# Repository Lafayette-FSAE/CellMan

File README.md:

# CellMan v2.2
A Cell Management Board for the Lafayette FSAE Accumulator Management System.

The purpose of CellMan is twofold. First, it is responsible for making and reporting
key measurements of the Cell it is mounted to. The most important of these are Voltage 
and Temperature, which are used by PacMan to determine if a fault condition has occured, and can also be used to help estimate State of Charge.
In addition, CellMan is capable of measuring the voltage of its Cell's negative terminal relative to the segment, used for determining its position, 
and some properties of its balancing circuit.

Each CellMan has also been equipped with an experimental Balancing Circuit, which can be used to allow active balancing of Cells within the same segment.
This is done through an isolated flyback converter, which pulls current from the cell it sits on, steps it up to the full segment voltage through an isolated
transformer, and outputs it back to the segment. A CellMan is capable of measuring the current being drawn from the cell by the flyback converter and the
voltage on its output side, and can report these back to PacMan along with the measurements mentioned above.

## Interface

Each CellMan is an I2C slave device, and can be controlled by a master, usually PacMan. All data reported to PacMan is sent over this interface, as well as commands
that control the high level behavior of CellMan.

While CellMan on different segments are electrically isolated from eachother, they occupy the same I2C bus, through 2 isolators on the PacMan board, and so their
addresses cannot conflict

### Reading Data

When data is requested from CellMan, it will report it over the bus, one byte at a time,  and always in the same order. An arbitrary number of bytes can be requested.

Most data is stored as 16 bit integers, and so is sent in 2 byte pairs, with the Least Significant Byte first, and the Most Significant Byte second.

Bytes are sent in the following order:

|Byte|0               |1               |2               |3              |4              |5            |6            |
|----|----------------|----------------|----------------|---------------|---------------|-------------|-------------|
|Data|Firmware Version|Cell Voltage LSB|Cell Voltage MSB|Temperature LSB|Temperature MSB|Position LSB |Position MSB |
|Unit|NA              |mV              |mV              |1/10 ºC        |1/10 ºC        |Raw ADC Value|Raw ADC Value|

Additional data can be added to the end of this as needed.

### Sending Commands

PacMan is controlled by writing data to one or more 16 bit registers. Each write command should be 3 bytes long, a 1 byte address, followed by 2 bytes of data.

Register addresses are organized as follows:

#### Calibration Parameters

While this feature is not currently supported, CellMan will eventually allow configuration of its many calibration functions for maximum accuracy.
Addresses from 0x01 to 0x0F have been reserved for this purpose.

|Address|Description      |
|-------|-----------------|
|0x01   |Temp Slope       |
|0x02   |Temp Offset      |
|0x03   |Balance Current Slope|
|0x04   |Balance Voltage Slope|

#### Balance Circuit

Addresses from 0x11 to 0x1F are reserved for registers which control the behavior of the Balance Circuit.
Currently, the circuit can be enabled or disabled, and the duty cycle and frequency of its control signal
can be changed.
0x14 is reserved for a Target Voltage parameter in order to allow support for a closed loop control scheme
to be used in the future. 

|Address|Description      |
|-------|-----------------|
|0x11   |Balance Enabled  |
|0x12   |Balance Duty Cycle|
|0x13   |Balance Frequency|
|0x14   |Target Voltage   |

#### Debug

0x23 controls the board's green LED, used for Debugging and feedback.

|Address|Description      |
|-------|-----------------|
|0x23   |Debug LED        |

## Schematic
[Link to PDF](https://sites.lafayette.edu/motorsports/files/2019/11/CellMan.pdf)

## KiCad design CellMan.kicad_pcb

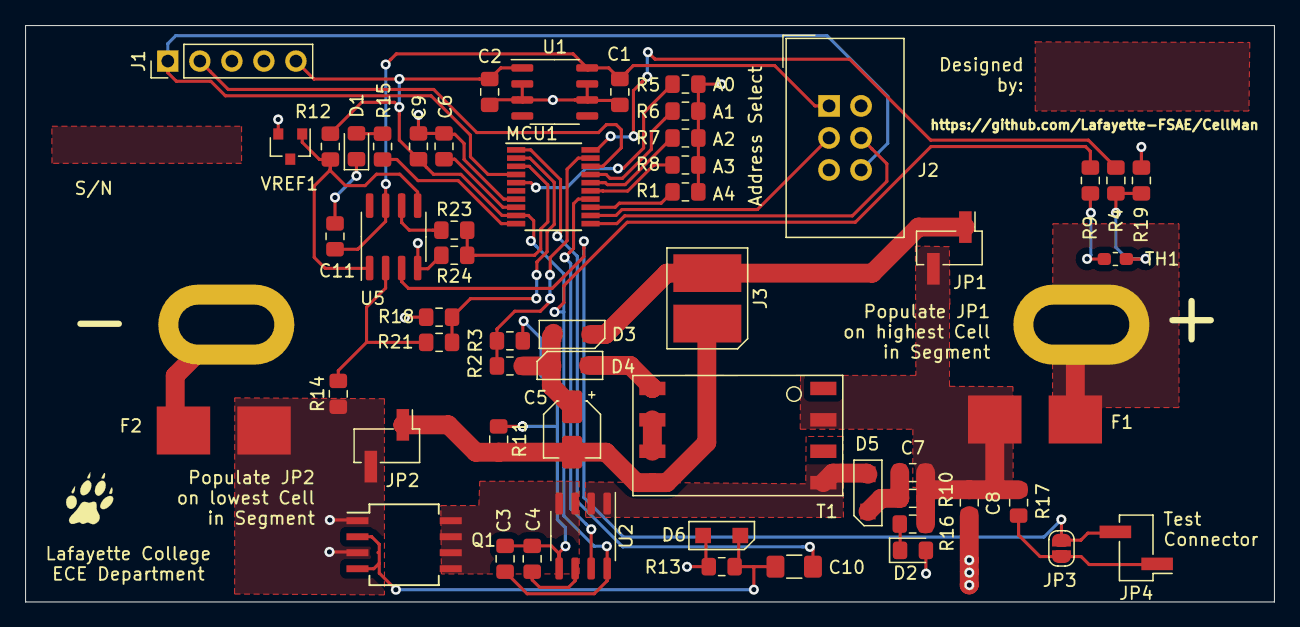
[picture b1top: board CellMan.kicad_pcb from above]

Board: 2 copper layers, 99.1 x 45.7 mm, 58 parts (0 on the bottom side), 43 nets.

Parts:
BT1: Battery_Cell; CELL60AH
C1: 0.33uF; C_0805_2012Metric_Pad1.15x1.40mm_HandSolder
C2, C3, C11: 0.1uF; C_0805_2012Metric_Pad1.15x1.40mm_HandSolder
C4: 1nF; C_0805_2012Metric_Pad1.15x1.40mm_HandSolder
C5: 1uF 50V; CP_Elec_4x5.4
C6, C8, C9: 1uF; C_0805_2012Metric_Pad1.15x1.40mm_HandSolder
C7: C; C_0805_2012Metric_Pad1.15x1.40mm_HandSolder
C10: 0.1uF 250V; C_1206_3216Metric_Pad1.42x1.75mm_HandSolder
D1: LED_Green; LED_0805_2012Metric_Pad1.15x1.40mm_HandSolder
D2: LED_Red; LED_0805_2012Metric_Pad1.15x1.40mm_HandSolder
D3, D4, D5, D6: 60V 2A; Diode_NTS260ESF
F1, F2: LittelfuseHolder; fuse_holder_smd_littelfuse
J1: Conn_01x05_Male; PinHeader_1x05_P2.54mm_Vertical
J2: IDC-Connector; IDC-Header_2x03_P2.54mm_Vertical
J3: AVX-IDC; AVX
JP1, JP2, JP4: Jumper; PinHeader_1x02_P2.54mm_Vertical_SMD_Pin1Left
JP3: SolderJumper_2_Open; SolderJumper-2_P1.3mm_Open_RoundedPad1.0x1.5mm
LOGO2: LeopardPawLogo; Paw
MCU1: STM8S003F3; TSSOP-20_4.4x6.5mm_P0.65mm
Q1: SP8K24FRATB; SO-8_5.3x6.2mm_P1.27mm
R1, R2, R3, R5, R6, R7, R8, R9, R10, R11, R12, R13, R15, R19: R; R_0805_2012Metric_Pad1.15x1.40mm_HandSolder
R4: 410; R_0805_2012Metric_Pad1.15x1.40mm_HandSolder
R14, R17, R23, R24: 2k; R_0805_2012Metric_Pad1.15x1.40mm_HandSolder
R16: 250; R_0805_2012Metric_Pad1.15x1.40mm_HandSolder
R18: 10k; R_0805_2012Metric_Pad1.15x1.40mm_HandSolder
R21: 51k; R_0805_2012Metric_Pad1.15x1.40mm_HandSolder
T1: FlybackTransformer; Transformer
TH1: NTCS0603; R_0603_1608Metric_Pad1.05x0.95mm_HandSolder
U1: L78L05CD13TR; SO-8_3.9x4.9mm_P1.27mm
U2: ACHS-7122; SO-8_3.9x4.9mm_P1.27mm
U5: AD8479; SOIC-8_3.9x4.9mm_P1.27mm
VREF1: ADR510; SOT-23

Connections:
+5V: C2.1, C9.1, J1.5, MCU1.9, R9.2, R12.1, U1.1, U2.8
+9V: C1.1, C11.1, J2.1, U1.8, U5.7
/A0: MCU1.5, R5.1
/A1: MCU1.17, R6.1
/A2: MCU1.16, R7.1
/A3: MCU1.15, R8.2
/A4: MCU1.13, R1.2
/Balance+: D3.1, J3.2, JP1.1
/Balance-: C5.2, J3.1, JP2.1, R11.2, T1.5
/Balance_ctl: C10.2, MCU1.1
/Balance_current: MCU1.14, U2.7
/Balance_feedback: MCU1.19, R2.2, R3.1
/Cell+: C7.1, C8.1, F1.1, JP1.2, R10.1, R16.1, R17.1, T1.2
/Cell+(RAW): BT1.1, F1.2
/Cell-: C8.2, D2.2, D6.2, F2.1, JP2.2, Q1.1, Q1.3, R13.2, R14.1
/Cell-(RAW): BT1.2, F2.2
/CellBalancing/Filter: C4.1, U2.6
/CellBalancing/LocalVout: C5.1, D3.2, D4.1, R2.1
/CellBalancing/ThisNetNeedsAName: Q1.5, Q1.6, Q1.7, Q1.8, U2.3, U2.4
/CellBalancing/ThisOneToo: D5.2, T1.4, U2.1, U2.2
/CellMeasurement/CellVoltage_RAW: R23.1, U5.6
/CellMeasurement/Vref: R12.2, U5.1, U5.5, VREF1.1
/CellTemp: MCU1.20, R4.1
/CellVoltage: MCU1.3, R23.2, R24.1
/DividedCell-: MCU1.2, R18.1, R21.2
/Ref_Cap: C6.2, MCU1.8
/Reset: J1.1, J2.6, MCU1.4
/SCL: J2.3, MCU1.12
/SDA: J2.4, MCU1.11
/SWIM: J1.2, MCU1.18
/User_LED: MCU1.10, R15.1
GND: C1.2, C2.2, C3.2, C4.2, C6.1, C9.2, C11.2, D1.1, J1.3, J2.2, J2.5, MCU1.7, R1.1, R3.2, R5.2, R6.2, R7.2, R8.1, R11.1, R19.1, R24.2, U1.2, U1.3, U1.6, U1.7, U2.5, U5.4, VREF1.2
unnamed: C7.2, D5.1, R10.2
unnamed: C10.1, D6.1, Q1.2, Q1.4, R13.1
unnamed: D1.2, R15.2
unnamed: D2.1, R16.2
unnamed: D4.2, T1.8
unnamed: JP3.1, JP4.1, R17.2
unnamed: JP3.2, JP4.2, U5.3
unnamed: R9.1, TH1.1
unnamed: R14.2, R21.1, U5.2
unnamed: R4.2, R19.2, TH1.2
unnamed: T1.6, T1.7

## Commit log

2019-09-21 Added Project to Git
2019-09-21 Added Most components
2019-09-21 Added Power and GND symbols to ADC Address Select
2019-09-21 Added Datasheets to I2C symbols
2019-09-24 Changed IO expander and added Reverse Polarity Protection
2019-09-24 Added some indicators and Debugging Pins
2019-09-24 Updated Cell Voltage Measurement
2019-09-24 Re-Plotted
2019-09-25 Added bypass capacitors to Power in and power out ports
2019-09-25 Changed GND net names
2019-09-27 finished adding diff amp
2019-10-02 started PCB layout
2019-10-03 continued work on layout
2019-10-04 layout continues
2019-10-04 finished placing components
2019-10-05 made mounting holes bigger
2019-10-06 fixed dip switch package
2019-10-08 layed out some more traces
2019-10-09 Routed more traces
2019-10-09 Ask Jon
2019-10-09 fixed ground plane issue
2019-10-09 added cutout in ground plane for safecellminus
2019-10-09 something minor
2019-10-09 zero unrouted traces baby
2019-10-11 memes
2019-10-15 Reviewed board, 10 unrouted traces to go
2019-10-16 Fixed some problems
2019-10-16 Fixed Temp Sensor Footprint
2019-10-17 mounting
2019-10-18 added solder mask for serial number
2019-10-18 made dimensions even
2019-10-24 archived version 0
2019-10-25 archived v0.7
2019-10-25 dropped some dead weight
2019-10-27 Started work on post-design review version
2019-10-28 Zero unrouted traces baby! Wait, where have I heard that before?
2019-10-28 adjusted mounting and added flair
2019-10-29 switched power supply to 24V (Seg+) and removed ADC
2019-11-01 idk, theres ovals now
2019-11-01 KiCad says there are no more traces to route, but my heart says otherwise
2019-11-01 approved?
2019-11-04 some cleaning up
2019-11-05 removed dip switch
2019-11-05 removed discrete divider circuitry
2019-11-05 Replaced discrete voltage divider and diff amp with AD8479
2019-11-06 cosmetic things
2019-11-06 unsure
2019-11-06 switched to 5V regulator
2019-11-07 cleaned up schematic a bit
2019-11-12 Replaced generic parts with parts in our custom library
2019-11-18 cleaned up schematic
2020-01-09 last commit
2020-01-09 drew draft of schematic
2020-01-10 Update to top level schematic
2020-01-10 More detailed Balance Circuit with specific parts
2020-01-10 Assigned schematics to footprints
2020-01-10 Assigned footprints to symbols
2020-01-11 Rearranged components to make more room for flyback converter
2020-01-11 Board Layout and routing
2020-01-11 Cleaned up silkscreen
2020-01-11 Updated Version Numbers
2020-01-11 updated gitignore
2020-01-19 Cell Balancing
2020-01-19 Updated Schematic
2020-01-19 Start of new layout
2020-01-19 WIP 1/19
2020-01-21 9 Unrouted Traces?
2020-01-21 Version 2.2 Review
2020-01-22 Who Cares
2020-01-23 Traces Routed
2020-01-23 Added Flair
2020-01-23 Removed Extra Mounting Holes
2020-01-23 Aesthetic changes
2020-01-23 More Tweaks
2020-01-24 Ready for spin
2020-01-27 Updated BOM
2020-02-04 Updated Gerbers
2020-02-04 switched cell mounting to non slotted
2020-02-04 remade gerbers
2020-02-25 Adding Resistor Values
2020-03-04 Updated Resistors Values
2020-03-13 Notes for Adam
2020-04-13 CAD Files and 3D models
